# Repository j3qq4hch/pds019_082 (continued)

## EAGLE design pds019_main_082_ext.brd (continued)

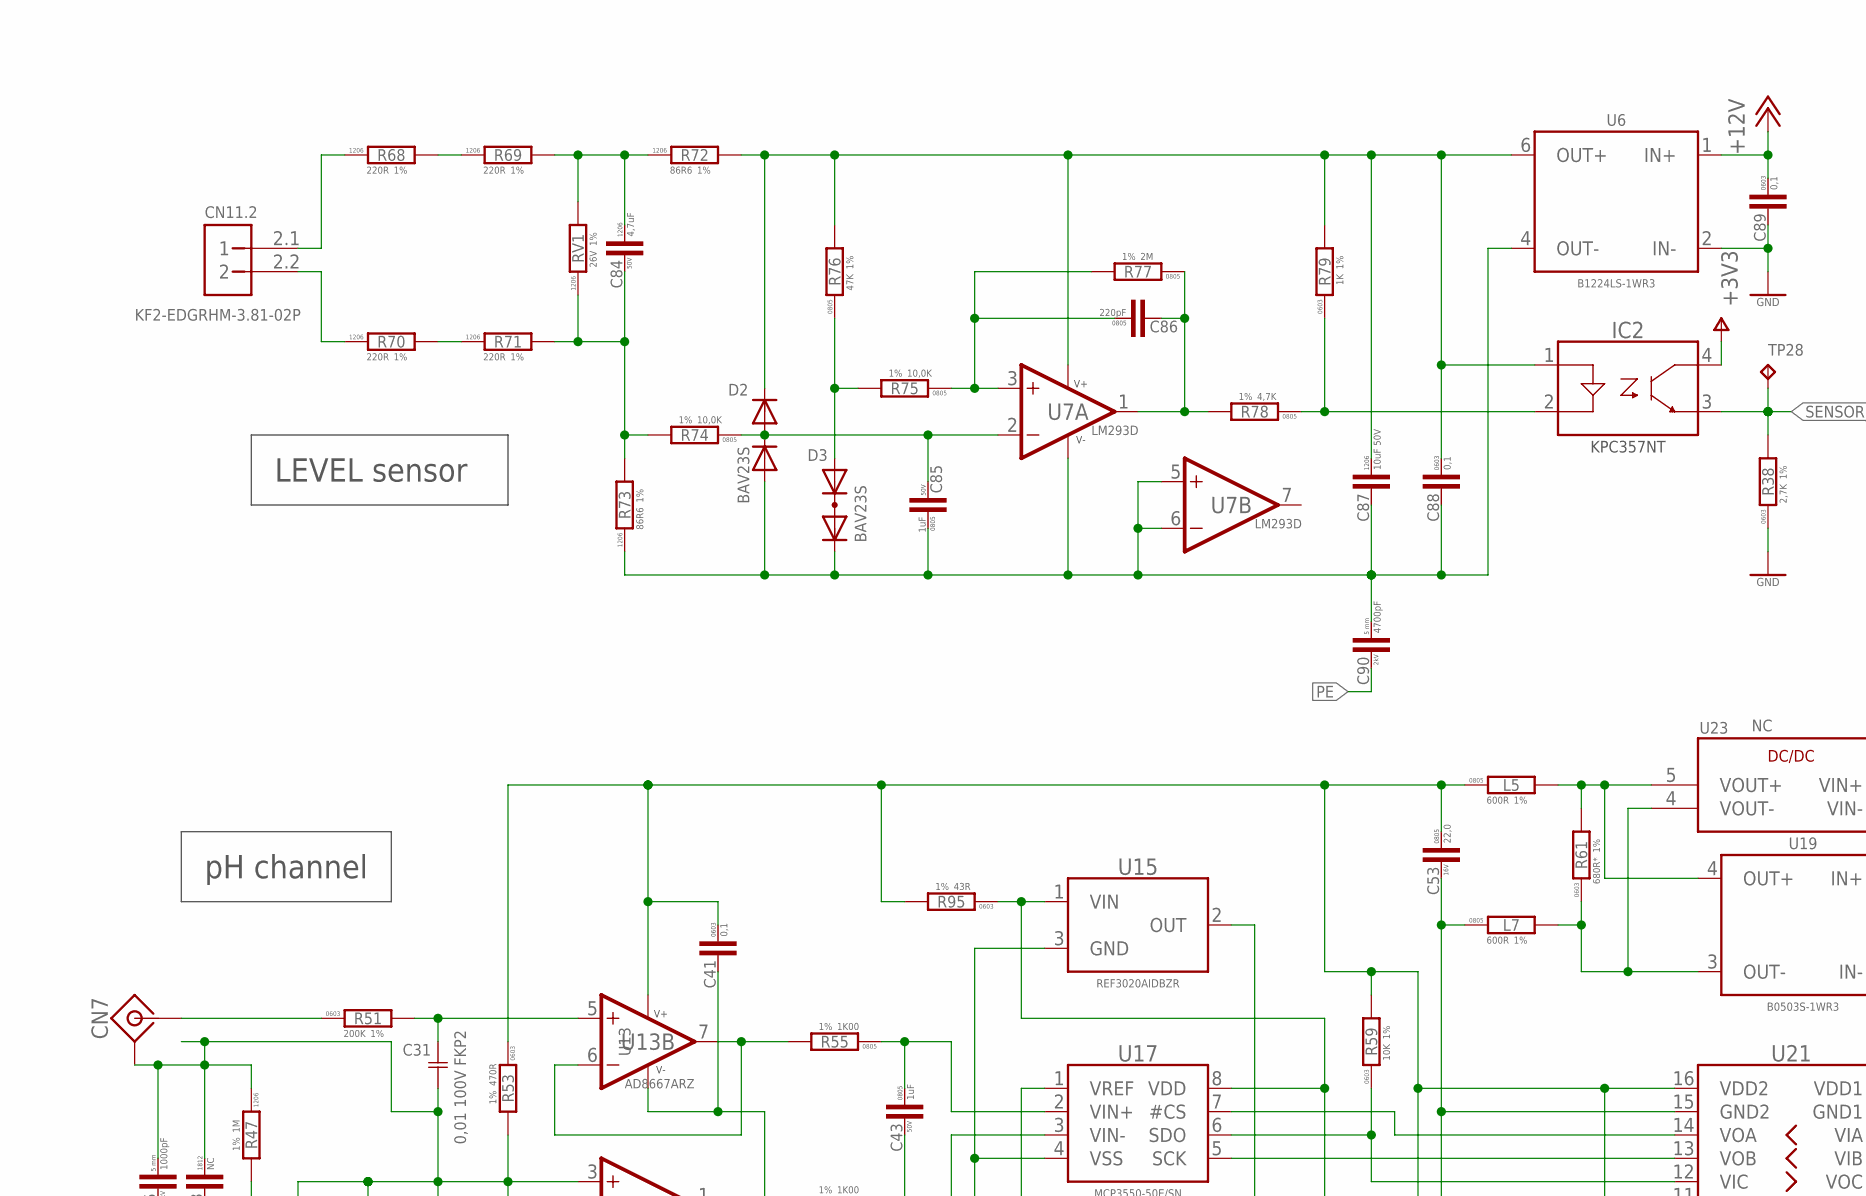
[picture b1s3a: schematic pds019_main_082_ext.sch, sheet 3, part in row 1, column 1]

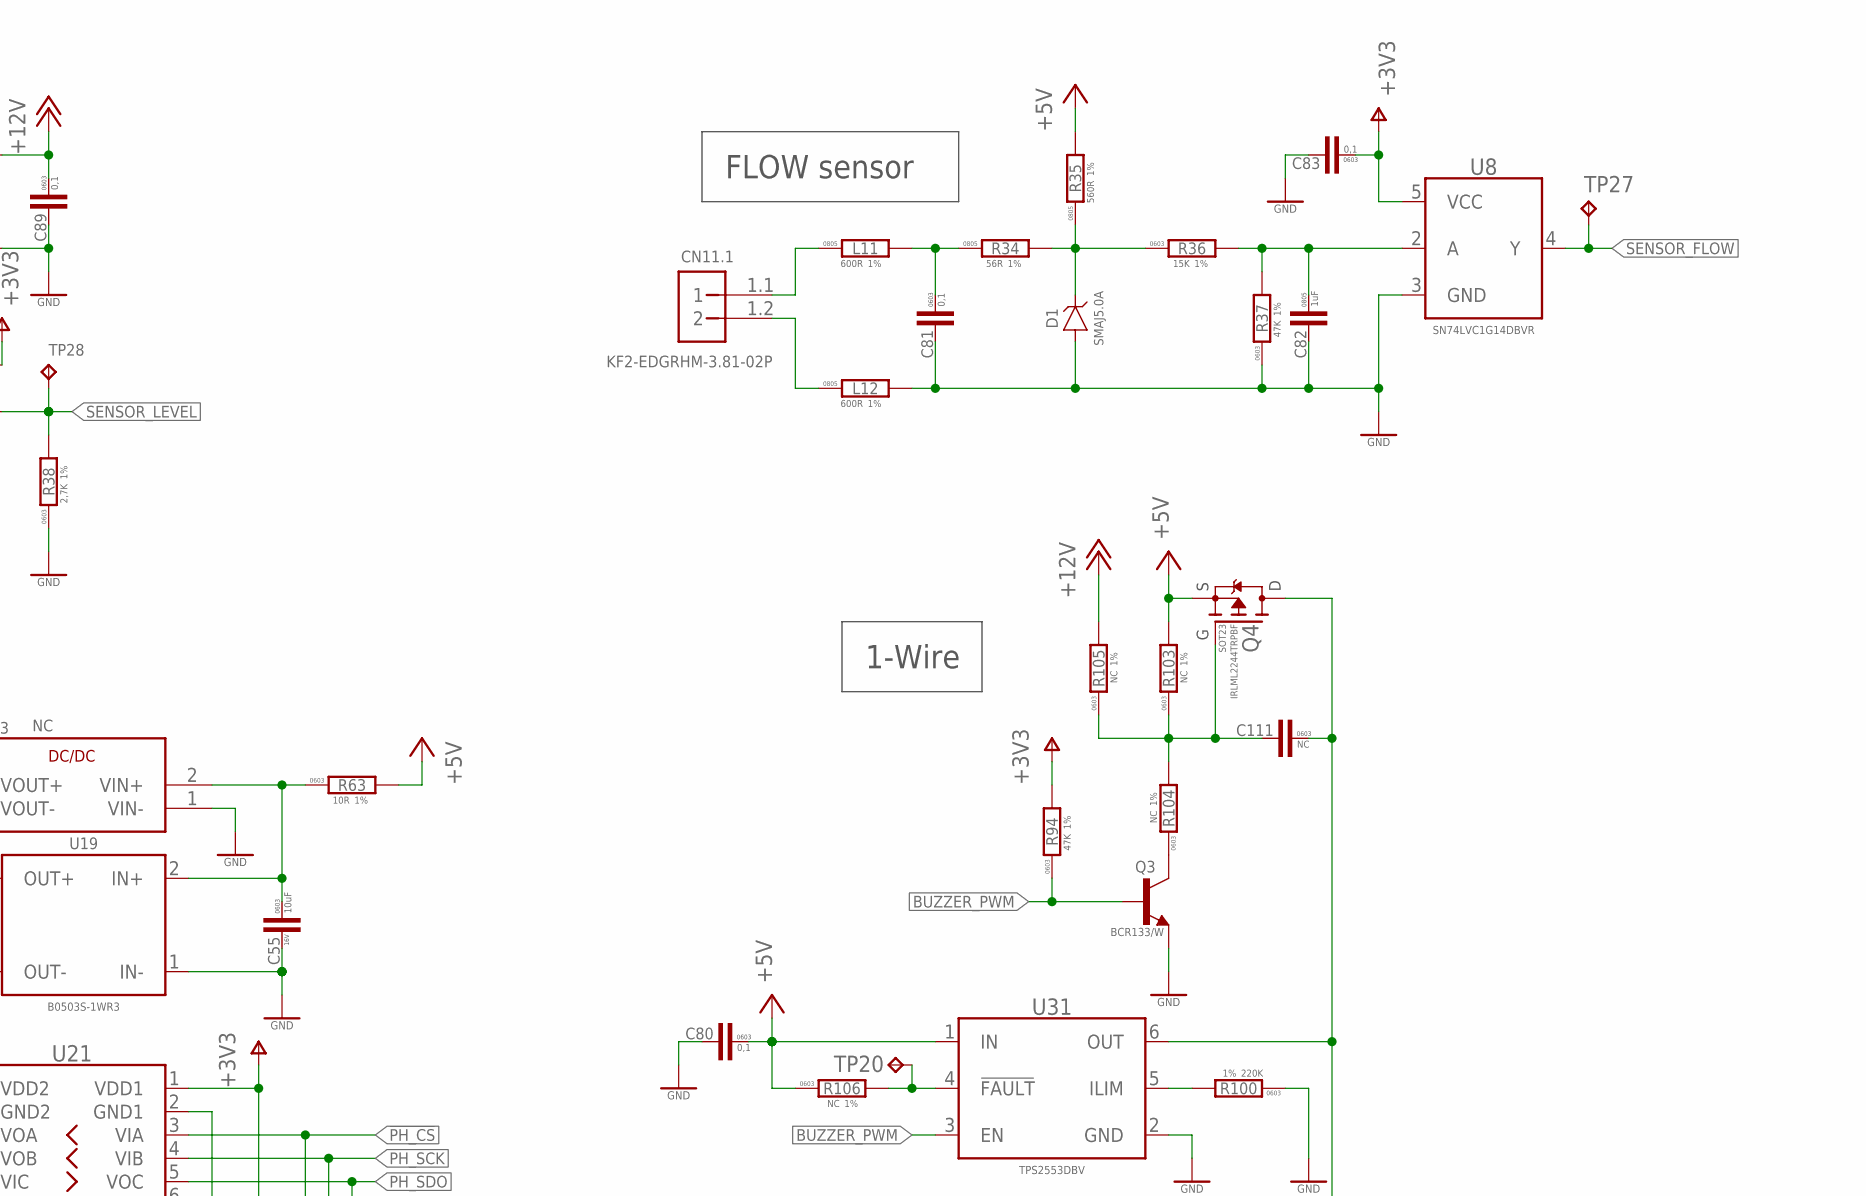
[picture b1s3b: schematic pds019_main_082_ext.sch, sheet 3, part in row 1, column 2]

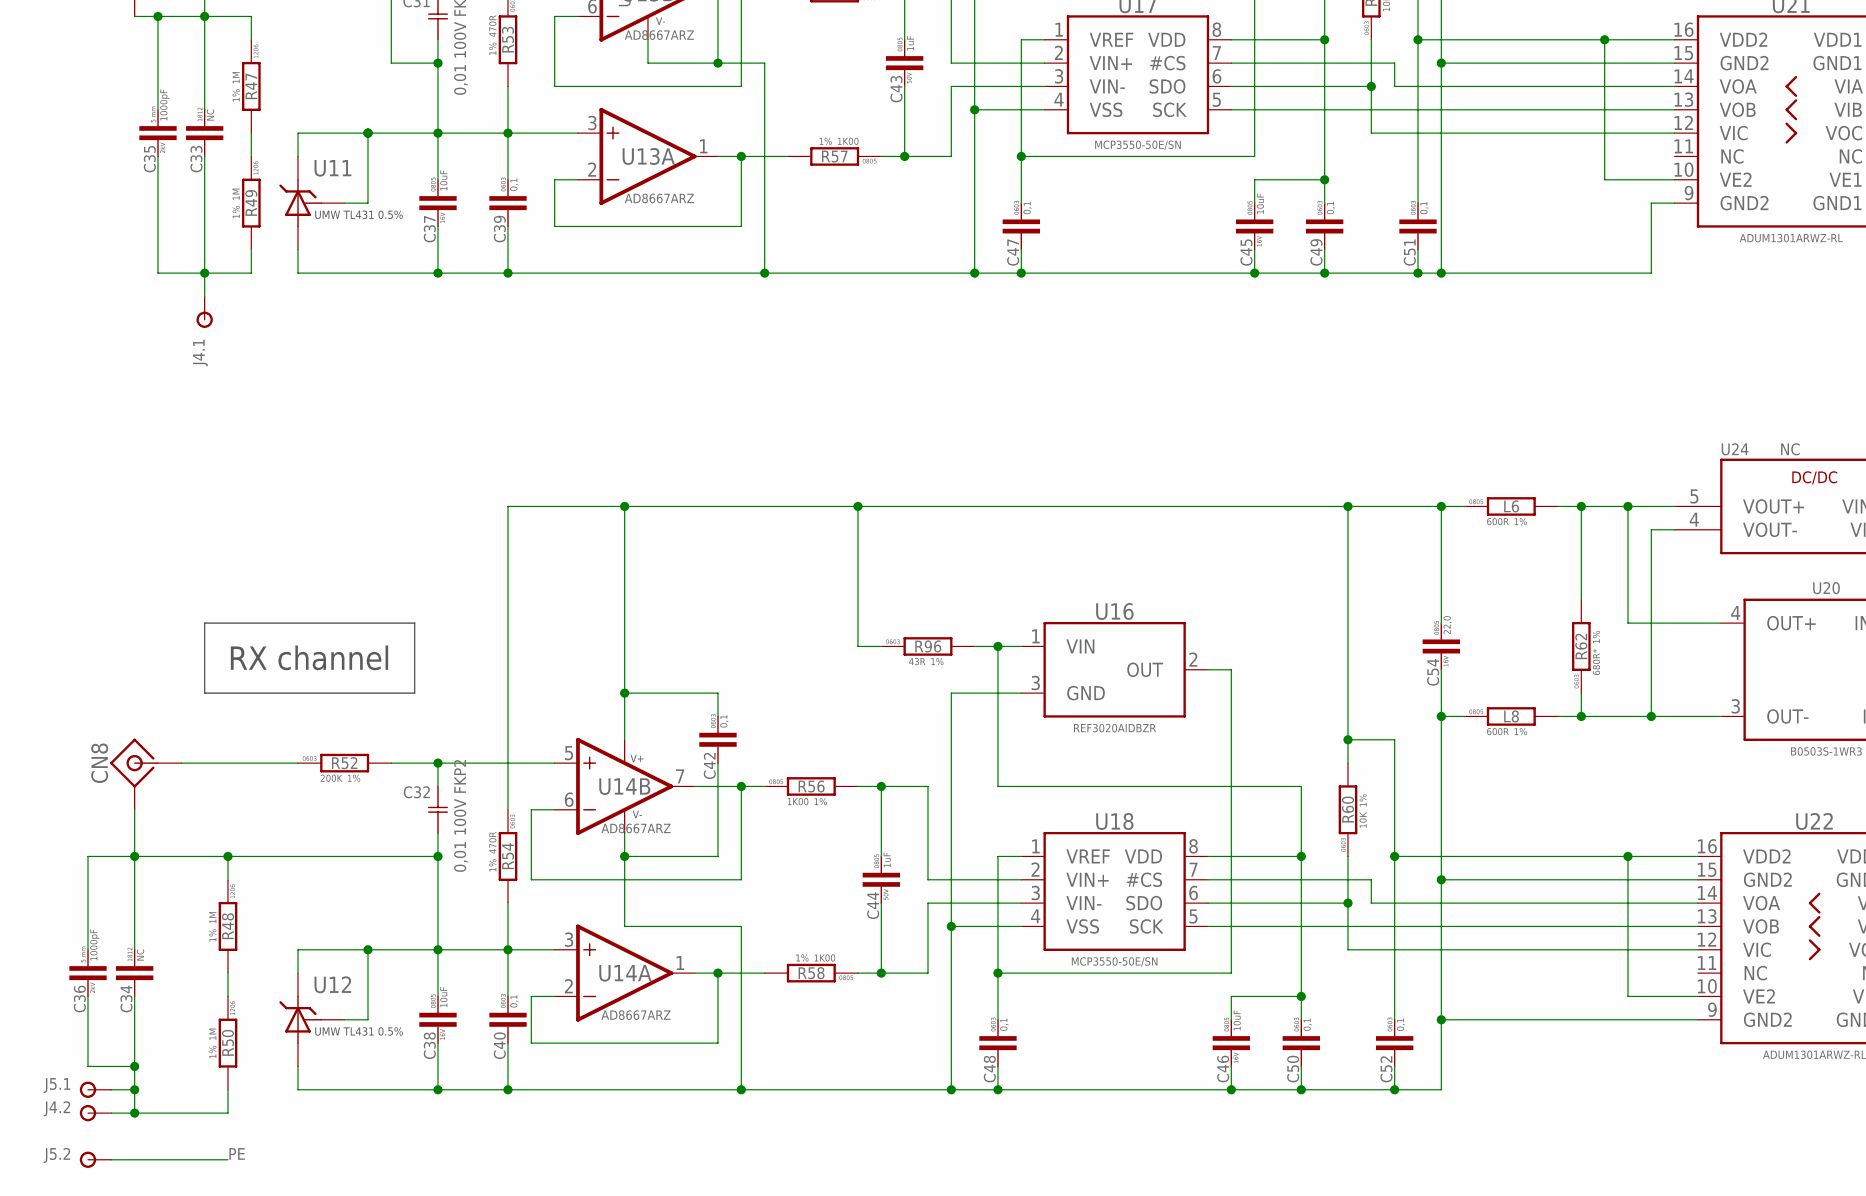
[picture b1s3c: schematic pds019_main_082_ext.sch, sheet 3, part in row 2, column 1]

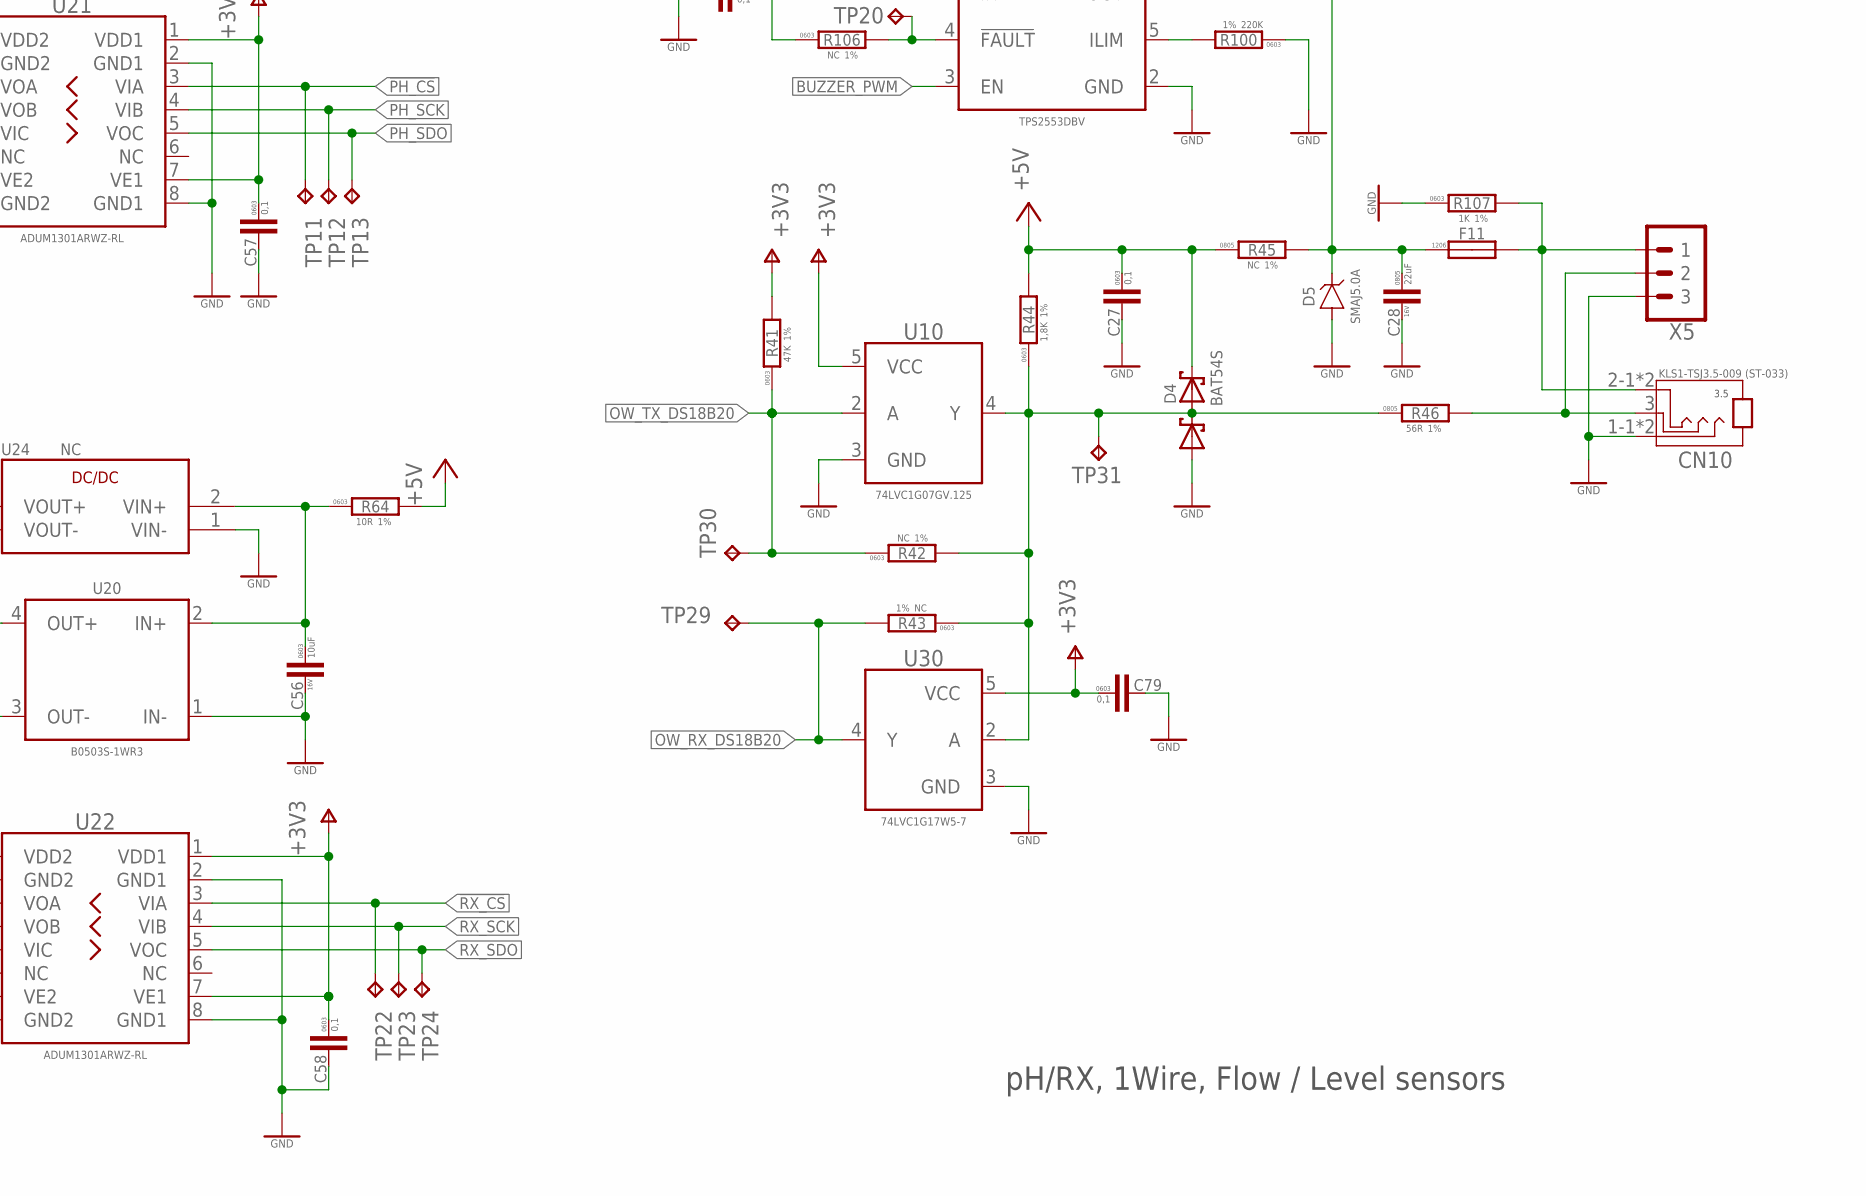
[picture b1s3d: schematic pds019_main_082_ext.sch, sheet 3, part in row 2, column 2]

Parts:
C27, C39, C40, C41, C42, C47, C48, C49, C50, C51, C52, C57, C58, C79, C80, C81, C83, C88, C89: 0,1; C0603
C28: 22uF; C0805; VOLTAGE 16V
C31, C32: 0,01 100V FKP2; C050-055X072
C33, C34: NC; C1812
C35, C36: 1000pF; C_5MM; VOLTAGE 2kV
C37, C38, C45, C46: 10uF; C0805; VOLTAGE 16V
C43, C44, C85: 1uF; C0805; VOLTAGE 50V
C53, C54: 22,0; C0805; VOLTAGE 16V
C55, C56: 10uF; C0603; VOLTAGE 16V
C82: 1uF; C0805
C84: 4,7uF; C1206; VOLTAGE 50V
C86: 220pF; C0805
C87: 10uF 50V; C1206
C90: 4700pF; C_5MM; VOLTAGE 2kV
C111: NC; C0603
CN7, CN8: RF_CONNECTOR-BNC-KY-WE; BNC_JR_CHN
CN10: ST-033
CN11: KF2-EDGRHM-3.81-02P; KF2EDGRHM-3.81-02P
D1, D5: SMAJ5.0A; DO-214AC(SMA)
D2, D3: BAV23S; SOT23-123
D4: BAT54S; SOT23
F11: NC; F1206
IC2: KPC357NT-SOP-4; -SOP-4
J4.1, J4.2, J5.1, J5.2: CONN_PAD-1,5R; CONN_PAD_1.5
L5, L6, L7, L8, L11, L12: 600R; R0805
Q3: NC; SOT23B-3
Q4: NC; SOT23
R34, R46: 56R; R0805
R35: 560R; R0805
R36: 15K; R0603
R37, R41, R94: 47K; R0603
R38: 2,7K; R0603
R42, R43, R103, R104, R105, R106: NC; R0603
R44: 1,8K; R0603
R45: NC; R0805
R47, R48, R49, R50: 1M; R1206
R51, R52: 200K; R0603
R53, R54: 470R; R0603
R55, R56, R57, R58: 1K00; R0805
R59, R60: 10K; R0603
R61, R62: 680R*; R0603
R63, R64: 10R; R0603
R68, R69, R70, R71: 220R; R1206
R72, R73: 86R6; R1206
R74, R75: 10,0K; R0805
R76: 47K; R0805
R77: 2M; R0805
R78: 4,7K; R0805
R79, R107: 1K; R0603
R95, R96: 43R; R0603
R100: 220K; R0603
RV1: 26V; R1206
TP11, TP12, TP13, TP20, TP22, TP23, TP24, TP27, TP28, TP29, TP30, TP31: TPTP16R; TP16R
U6: B1224LS-1WR3; SIP7_6X19.65_SINGLE
U7: LM293D; SOIC8
U8: 74LVC1G14DBV; SOT23-5
U10: 74LVC1G07GV; SOT23-5
U11, U12: TL431; SOT23B-3
U13, U14: AD8667ARZ-SO8; SOIC8
U15, U16: REF3020AIDBZ; SOT23B-3
U17, U18: MCP3550; SOIC8
U19, U20: B0503S-1WR3; SIP-4
U21, U22: ISO7231CDW; SO-16W
U23, U24: NC; PSDV_ELF_2
U30: 74LVC1G17; SOT23-5
U31: TPS2553DBV; SOT23-6
X5: PINHEAD_1X03-2.54; 1X03-PTH-2.54

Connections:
!PH_CS: TP11.TP, U21.3 (VIA); also elsewhere on the board
!RX_CS: TP22.TP, U22.3 (VIA); also elsewhere on the board
+3V3: C57.1, C58.1, C79.1, C83.1, IC2.4 (COLLECTOR), R41.2, R94.2, U8.5 (VCC), U10.5 (VCC), U21.1 (VDD1), U21.7 (VE1), U22.1 (VDD1), U22.7 (VE1), U30.5 (VCC); also elsewhere on the board
+5V: C27.1, C80.1, D4.2 (C2), Q4.2 (S), R35.2, R44.2, R45.1, R63.2, R64.2, R103.2, R106.1, U31.1 (IN); also elsewhere on the board
+12V: C89.1, R105.2, U6.1 (IN+); also elsewhere on the board
BUZZER_PWM: Q3.1 (B), R94.1, U31.3 (EN); also elsewhere on the board
GND: C27.2, C28.2, C55.2, C56.2, C57.2, C58.2, C79.2, C80.2, C81.2, C82.2, C83.2, C89.2, CN10.1-1 (S), CN10.1-2 (S), D1.A, D4.1 (A1), D5.A, L12.2, Q3.2 (E), R37.1, R38.1, R100.1, R107.1, U6.2 (IN-), U8.3 (GND), U10.3 (GND), U19.1 (IN-), U20.1 (IN-), U21.2 (GND1), U21.8 (GND1), U22.2 (GND1), U22.8 (GND1), U23.1 (VIN-), U24.1 (VIN-), U30.3 (GND), U31.2 (GND), X5.3; also elsewhere on the board
LVL_24V: C87.P$1 (1), C88.1, D2.2 (C2), IC2.1 (A), R72.P$2 (2), R76.2, R79.2, U6.6 (OUT+), U7.8 (V+)
LVL_GND: C85.1, C87.P$2 (2), C88.2, C90.1, D2.1 (A1), D3.2 (C2), R73.P$1 (1), U6.4 (OUT-), U7.4 (V-), U7.5 (IN+), U7.6 (IN-)
LVL_SNS+: CN11.2.1 (1), R68.P$1 (1)
LVL_SNS-: CN11.2.2 (2), R70.P$1 (1)
unnamed: CN7.1 (ANT), R51.1
unnamed: CN8.1 (ANT), R52.1
unnamed: C32.1, R52.2, U14.5 (IN+)
unnamed: R106.2, TP20.TP, U31.4 (!FAULT)
unnamed: IC2.2 (C), R78.1, R79.1
unnamed: C46.1, C50.1, R96.2, U16.1 (VIN), U18.8 (VDD)
unnamed: C45.1, C49.1, R95.1, U15.1 (VIN), U17.8 (VDD)
unnamed: C28.1, C111.1, D5.C, F11.P$1 (1), Q4.3 (D), R45.2, U31.6 (OUT)
unnamed: C86.2, R77.1, R78.2, U7.1 (OUT)
unnamed: R48.P$2 (2), R50.P$1 (1)
unnamed: L5.2, R61.2, U19.4 (OUT+), U23.5 (VOUT+)
unnamed: C85.2, D2.3 (C1A2), R74.1, U7.2 (IN-)
unnamed: C81.1, L11.2, R34.1
unnamed: L7.2, R61.1, U19.3 (OUT-), U23.4 (VOUT-)
unnamed: L6.2, R62.2, U20.4 (OUT+), U24.5 (VOUT+)
unnamed: L8.2, R62.1, U20.3 (OUT-), U24.4 (VOUT-)
unnamed: C84.P$1 (1), R69.P$2 (2), R72.P$1 (1), RV1.P$2 (2)
unnamed: CN11.1.1 (1), L11.1
unnamed: R47.P$2 (2), R49.P$1 (1)
unnamed: CN11.1.2 (2), L12.1
unnamed: R68.P$2 (2), R69.P$1 (1)
unnamed: D1.C, R34.2, R35.1, R36.1
unnamed: C55.1, R63.1, U19.2 (IN+), U23.2 (VIN+)
unnamed: C56.1, R64.1, U20.2 (IN+), U24.2 (VIN+)
unnamed: R70.P$2 (2), R71.P$1 (1)
unnamed: R100.2, U31.5 (ILIM)
unnamed: C86.1, R75.1, R77.2, U7.3 (IN+)
unnamed: D3.1 (A1), R75.2, R76.1
unnamed: Q3.3 (C), R104.1
unnamed: C84.P$2 (2), R71.P$2 (2), R73.P$2 (2), R74.2, RV1.P$1 (1)
unnamed: C111.2, Q4.1 (G), R103.1, R104.2, R105.1
unnamed: D4.3 (C1A2), R42.2, R43.1, R44.1, R46.1, TP31.TP, U10.4 (Y), U30.2 (A)
unnamed: C82.1, R36.2, R37.2, U8.2 (A)
unnamed: CN10.2-1 (T), CN10.2-2 (T), F11.P$2 (2), R107.2, X5.1
unnamed: CN10.3 (R), R46.2, X5.2
OW_RX_DS18B20: R43.2, TP29.TP, U30.4 (Y); also elsewhere on the board
OW_TX_DS18B20: R41.1, R42.1, TP30.TP, U10.2 (A); also elsewhere on the board
PE: C90.2, J5.2.1; also elsewhere on the board
PE_PH: C33.P$2 (2), C35.2, J4.1.1, R49.P$2 (2)
PE_RX: C34.P$2 (2), C36.2, J4.2.1, J5.1.1, R50.P$2 (2)
PHADC+: C43.1, R55.1, U17.2 (VIN+)
PHADC-: C43.2, R57.1, U17.3 (VIN-)
PH_ADCCS: U17.7 (#CS), U21.14 (VOA)
PH_ADCSCK: U17.5 (SCK), U21.13 (VOB)
PH_ADCSDO: R59.1, U17.6 (SDO), U21.12 (VIC)
PH_AMP_VO+: R55.2, U13.6 (IN-), U13.7 (OUT)
PH_AMP_VO-: R57.2, U13.1 (OUT), U13.2 (IN-)
PH_GND: C37.2, C39.2, C41.2, C45.2, C47.2, C49.2, C51.2, C53.2, L7.1, U11.3 (A), U13.4 (V-), U15.3 (GND), U17.4 (VSS), U21.9 (GND2), U21.15 (GND2)
PH_SCK: TP12.TP, U21.4 (VIB); also elsewhere on the board
PH_SDO: TP13.TP, U21.5 (VOC); also elsewhere on the board
PH_VCC: C41.1, C51.1, C53.1, L5.1, R53.1, R59.2, R95.2, U13.8 (V+), U21.10 (VE2), U21.16 (VDD2)
PH_VCOM: C31.2, C33.P$1 (1), C35.1, C37.1, C39.1, CN7.M1 (GND), CN7.M2 (GND), CN7.M3 (GND), CN7.M4 (GND), R47.P$1 (1), R53.2, U11.1 (R), U11.2 (C), U13.3 (IN+)
PH_VINF: C31.1, R51.2, U13.5 (IN+)
PH_VREF: C47.1, U15.2 (OUT), U17.1 (VREF)
RXADC+: C44.1, R56.2, U18.2 (VIN+)
RXADC-: C44.2, R58.1, U18.3 (VIN-)
RX_ADCCS: U18.7 (#CS), U22.14 (VOA)
RX_ADCSCK: U18.5 (SCK), U22.13 (VOB)
RX_ADCSDO: R60.1, U18.6 (SDO), U22.12 (VIC)
RX_AMP_VO+: R56.1, U14.6 (IN-), U14.7 (OUT)
RX_AMP_VO-: R58.2, U14.1 (OUT), U14.2 (IN-)
RX_COM: C32.2, C34.P$1 (1), C36.1, C38.1, C40.1, CN8.M1 (GND), CN8.M2 (GND), CN8.M3 (GND), CN8.M4 (GND), R48.P$1 (1), R54.2, U12.1 (R), U12.2 (C), U14.3 (IN+)
RX_GND: C38.2, C40.2, C42.2, C46.2, C48.2, C50.2, C52.2, C54.2, L8.1, U12.3 (A), U14.4 (V-), U16.3 (GND), U18.4 (VSS), U22.9 (GND2), U22.15 (GND2)
RX_SCK: TP23.TP, U22.4 (VIB); also elsewhere on the board
RX_SDO: TP24.TP, U22.5 (VOC); also elsewhere on the board
RX_VCC: C42.1, C52.1, C54.1, L6.1, R54.1, R60.2, R96.1, U14.8 (V+), U22.10 (VE2), U22.16 (VDD2)
RX_VREF: C48.1, U16.2 (OUT), U18.1 (VREF)
SENSOR_FLOW: TP27.TP, U8.4 (Y); also elsewhere on the board
SENSOR_LEVEL: IC2.3 (EMITTER), R38.2, TP28.TP; also elsewhere on the board

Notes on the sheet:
1-Wire
pH/RX, 1Wire, Flow / Level sensors
FLOW sensor
LEVEL sensor
pH channel
RX channel

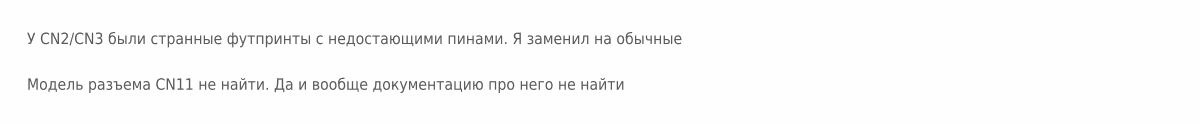
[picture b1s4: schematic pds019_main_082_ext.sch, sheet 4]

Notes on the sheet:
У CN2/CN3 были странные футпринты с недостающими пинами. Я заменил на обычные
Модель разъема CN11 не найти. Да и вообще документацию про него не найти

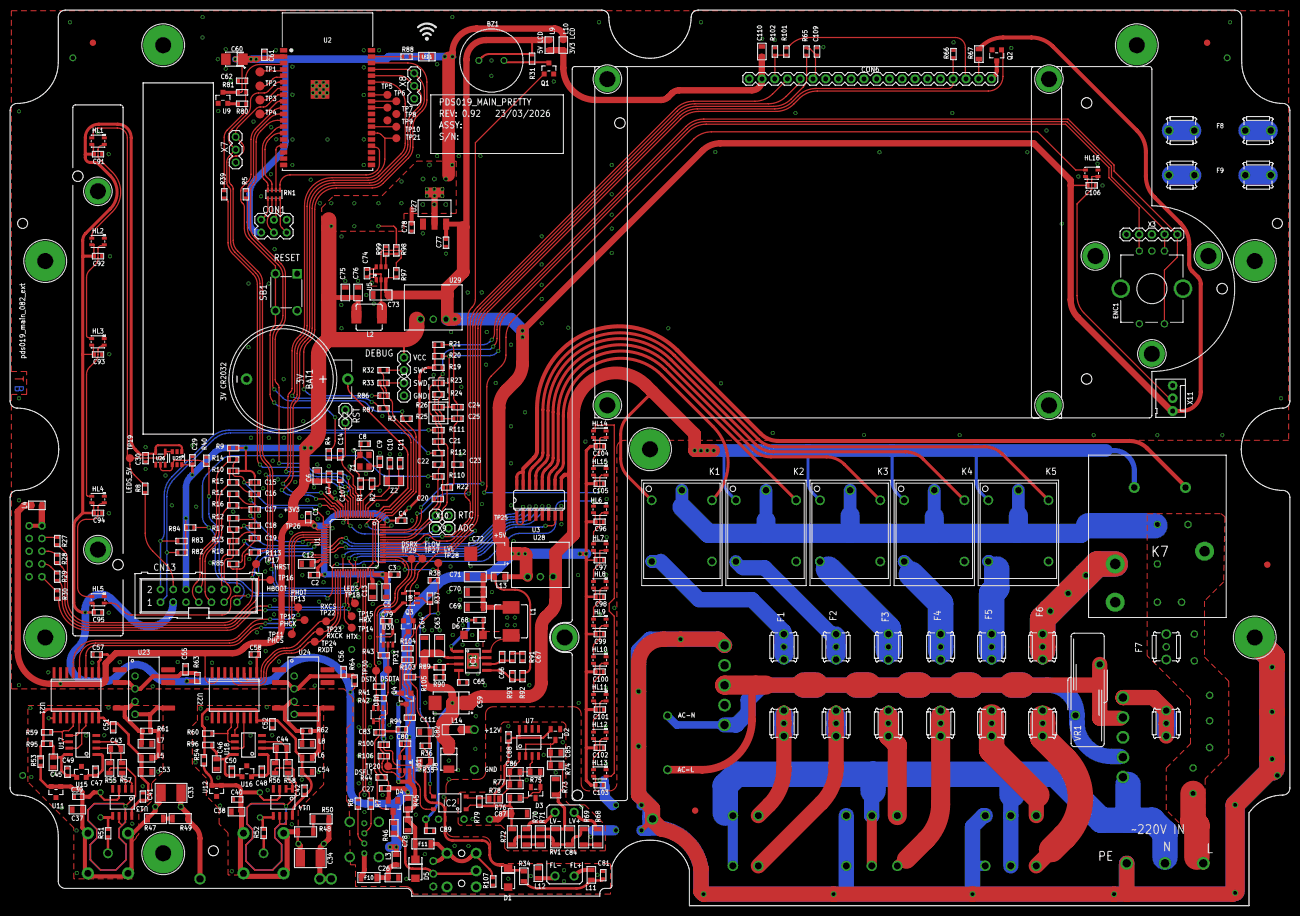
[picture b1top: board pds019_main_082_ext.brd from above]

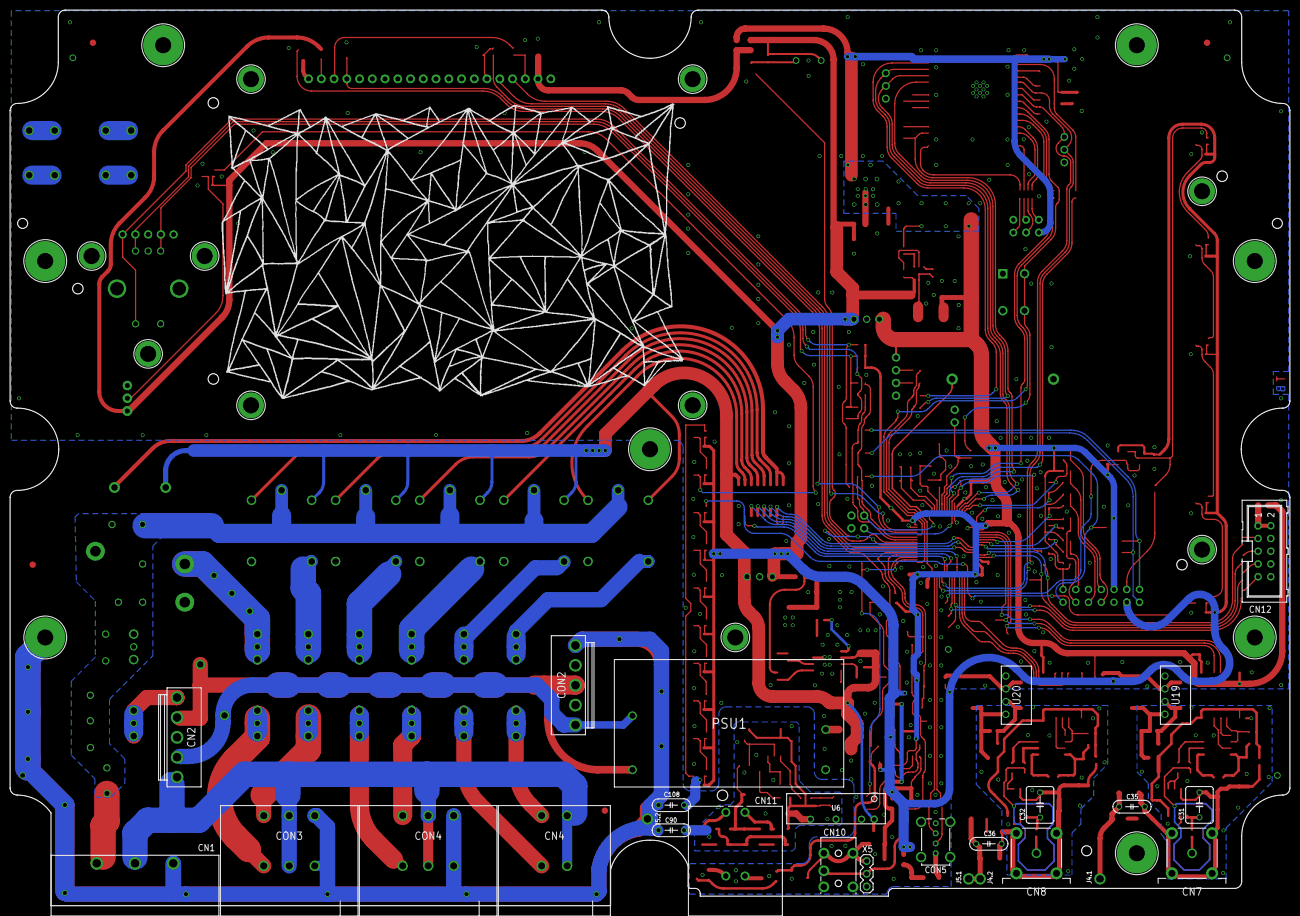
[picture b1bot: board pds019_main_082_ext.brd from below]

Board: 2 copper layers, 255.0 x 178.4 mm, 410 parts (28 on the bottom side), 238 nets.

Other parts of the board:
BOX1: BOX_G3783MF-IP67_MM
COVER1: PDS019_COVER_SW_LED
COVER2: PDS019_COVER_LEDS
COVER3: PDS019_COVER_ENC
REP1, REP2, REP3, REP4: REF_POINT_D1.27_D3.81
U$1: LCD12864_93X70_CHINA_SILK
U$2: ART

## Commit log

2026-03-19 initial import
2026-03-21 some progress
2026-03-22 its done now
2026-03-22 readme
